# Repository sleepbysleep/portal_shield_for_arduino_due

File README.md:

# portal_shield_for_arduino_due
KiCad project - 2 x RS232 with RS485 option, 1 x relay, and 1 x opto-coupler

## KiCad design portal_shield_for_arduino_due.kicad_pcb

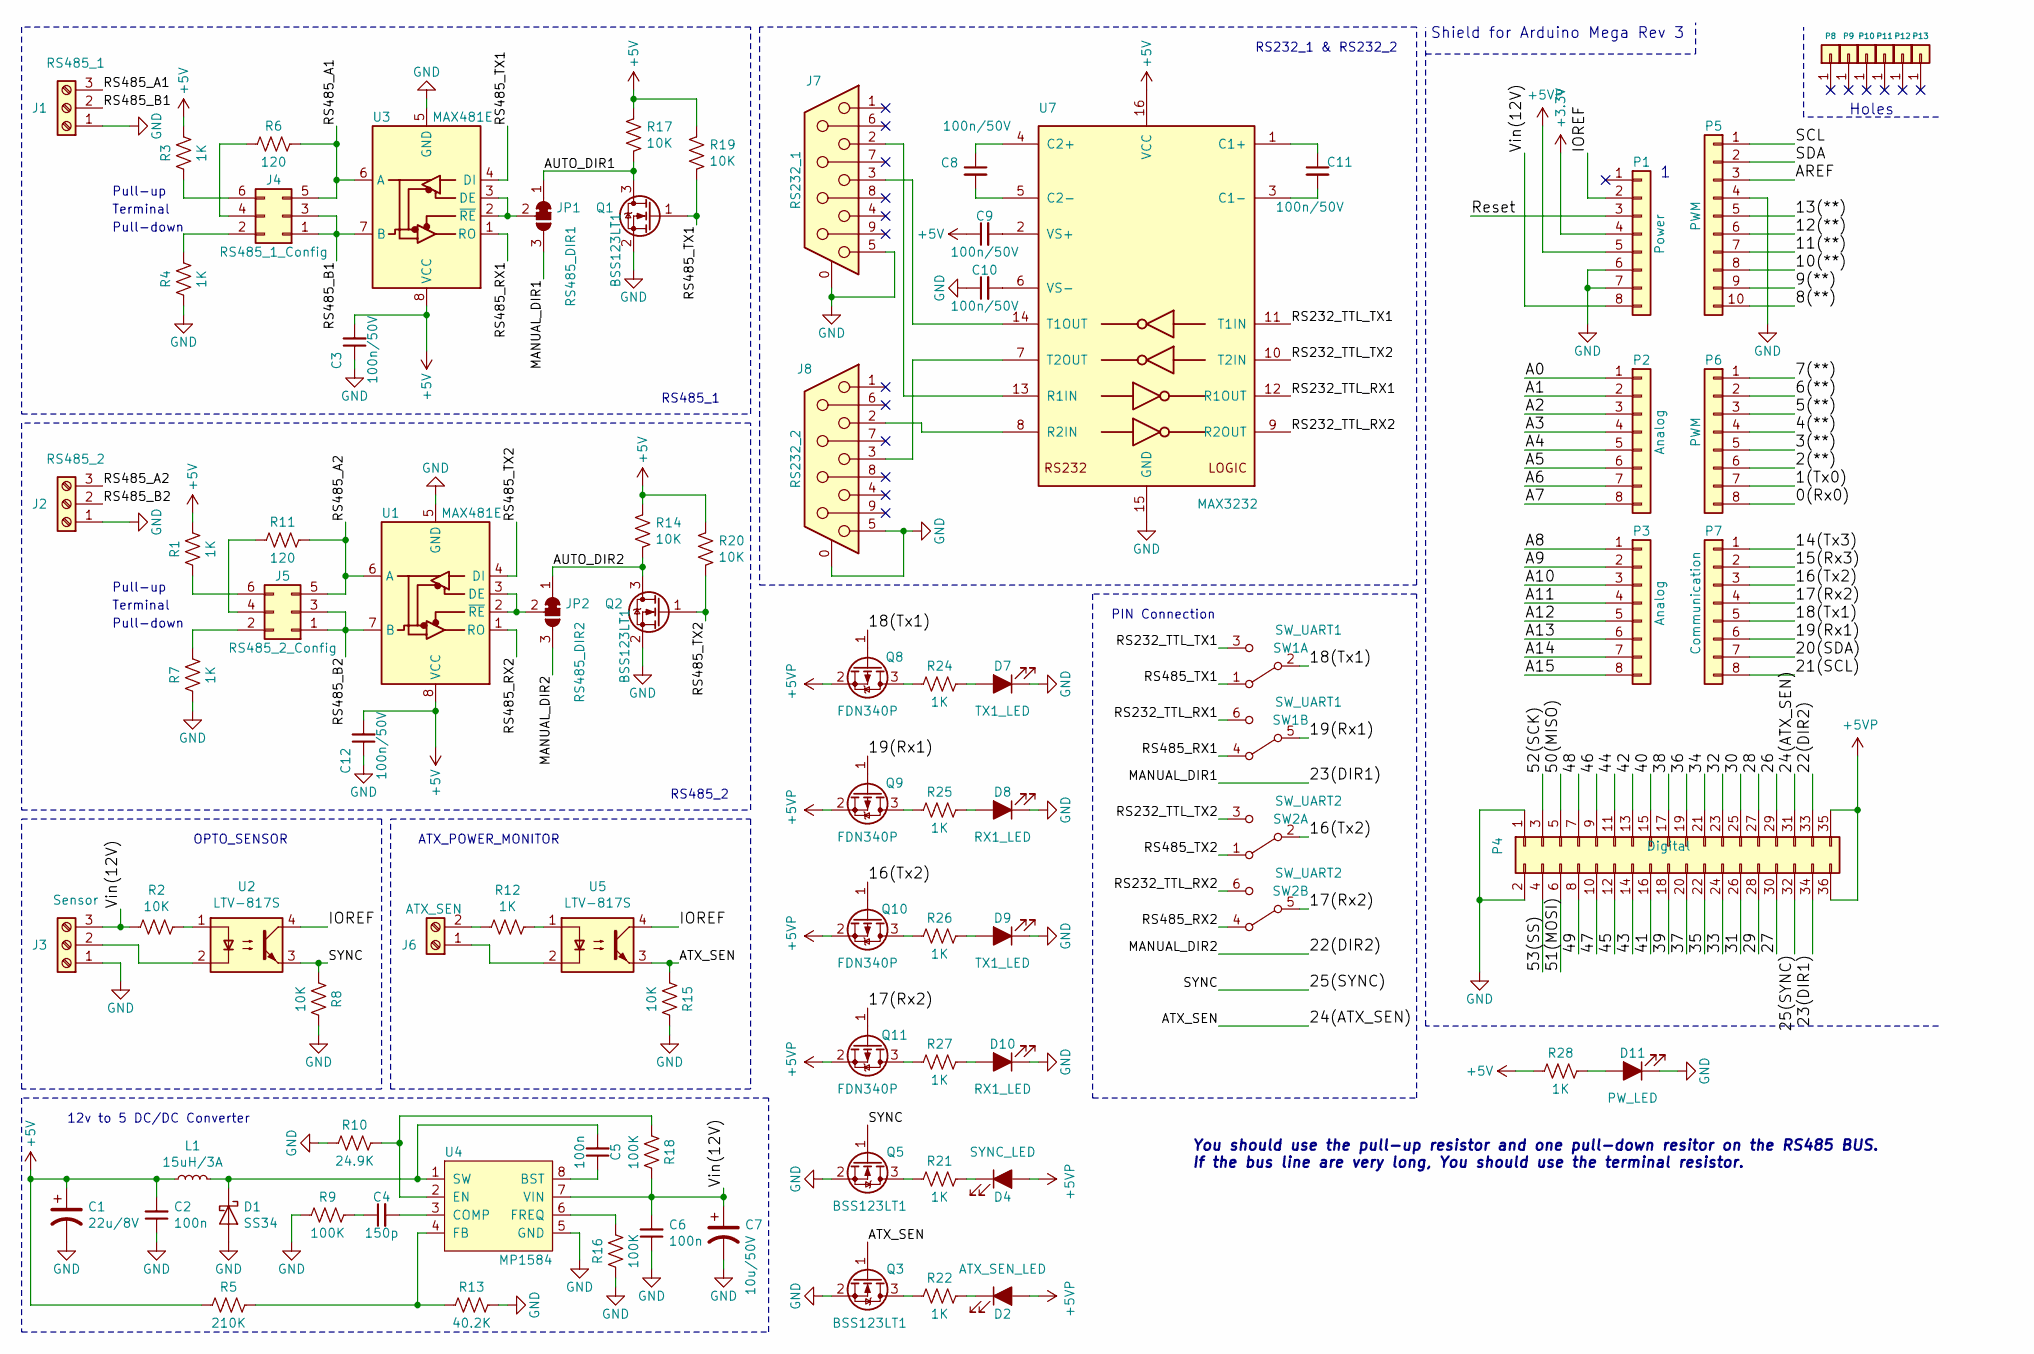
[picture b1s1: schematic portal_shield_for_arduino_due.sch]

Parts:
C1: 22u/8V; C_1206_3216Metric
C2, C5, C6: 100n; C_0805_2012Metric
C3, C8, C9, C10, C11, C12: 100n/50V; C_0805_2012Metric
C4: 150p; C_0805_2012Metric
C7: 10u/50V; C_1206_3216Metric
D1: SS34; D_SOD-123F
D2: ATX_SEN_LED; LED_0805_2012Metric
D4: SYNC_LED; LED_0805_2012Metric
D7, D9: TX1_LED; LED_0805_2012Metric
D8, D10: RX1_LED; LED_0805_2012Metric
D11: PW_LED; LED_0805_2012Metric
J1: RS485_1; TerminalBlock_Phoenix_PTSA-1,5-3-3.5-Z_1x3_P3.5mm_Vertical
J2: RS485_2; TerminalBlock_Phoenix_PTSA-1,5-3-3.5-Z_1x3_P3.5mm_Vertical
J3: Sensor; TerminalBlock_Phoenix_PTSA-1,5-3-3.5-Z_1x3_P3.5mm_Vertical
J4: RS485_1_Config; PinHeader_2x03_P2.54mm_Vertical
J5: RS485_2_Config; PinHeader_2x03_P2.54mm_Vertical
J6: ATX_SEN; TerminalBlock_Phoenix_PTSA-1,5-2-3.5-Z_1x2_P3.5mm_Vertical
J7: RS232_1; DSUB-9_Female_Vertical_P2.77x2.84mm_MountingHoles
J8: RS232_2; DSUB-9_Female_Vertical_P2.77x2.84mm_MountingHoles
JP1: RS485_DIR1; SolderJumper-3_P1.3mm_Open_Pad1.0x1.5mm
JP2: RS485_DIR2; SolderJumper-3_P1.3mm_Open_Pad1.0x1.5mm
L1: 15uH/3A; L_Abracon_ASPI_0630LR
P1: Power; Socket_Strip_Arduino_1x08
P2, P3: Analog; Socket_Strip_Arduino_1x08
P4: Digital; Socket_Strip_Arduino_2x18
P5: PWM; Socket_Strip_Arduino_1x10
P6: PWM; Socket_Strip_Arduino_1x08
P7: Communication; Socket_Strip_Arduino_1x08
P8, P9, P10, P11, P12, P13: CONN_01X01; Arduino_1pin
Q1, Q2, Q3, Q5: BSS123LT1; SOT-23
Q8, Q9, Q10, Q11: FDN340P; SOT-23
R1, R3, R4, R7, R12, R21, R22, R24, R25, R26, R27, R28: 1K; R_0805_2012Metric
R2, R8, R14, R15, R17, R19, R20: 10K; R_0805_2012Metric
R5: 210K; R_0805_2012Metric
R6, R11: 120; R_0805_2012Metric
R9, R16, R18: 100K; R_0805_2012Metric
R10: 24.9K; R_0805_2012Metric
R13: 40.2K; R_0805_2012Metric
SW1: SW_UART1; SW_CK_AYZ020AGRLC_DPDT_Straight
SW2: SW_UART2; SW_CK_AYZ020AGRLC_DPDT_Straight
U1, U3: MAX481E; SOIC-8_3.9x4.9mm_P1.27mm
U2, U5: LTV-817S; SMDIP-4_W9.53mm
U4: MP1584; SOIC8E
U7: MAX3232; TSSOP-16_4.4x5mm_P0.65mm

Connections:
+3V3: P1.4
+5V: C1.1, C2.2, C3.2, C9.1, C12.2, L1.1, R1.1, R3.1, R5.2, R14.1, R17.1, R19.1, R20.1, R28.2, U1.8 (VCC), U3.8 (VCC), U7.16 (VCC)
+5VP: D2.2 (A), D4.2 (A), P1.5, P4.35, P4.36, Q8.2 (S), Q9.2 (S), Q10.2 (S), Q11.2 (S)
/0(Rx0): P6.8
/1(Tx0): P6.7
/2(**): P6.6
/3(**): P6.5
/4(**): P6.4
/5(**): P6.3
/6(**): P6.2
/7(**): P6.1
/8(**): P5.10
/9(**): P5.9
/10(**): P5.8
/11(**): P5.7
/12(**): P5.6
/13(**): P5.5
/14(Tx3): P7.1
/15(Rx3): P7.2
/16(Tx2): P7.3, Q10.1 (G), SW2.2 (B)
/17(Rx2): P7.4, Q11.1 (G), SW2.5 (B)
/18(Tx1): P7.5, Q8.1 (G), SW1.2 (B)
/19(Rx1): P7.6, Q9.1 (G), SW1.5 (B)
/20(SDA): P7.7
/21(SCL): P7.8
/22(DIR2): JP2.3 (B), P4.33
/23(DIR1): JP1.3 (B), P4.34
/24(ATX_SEN): P4.31, Q3.1 (G), R15.2, U5.3
/25(SYNC): P4.32, Q5.1 (G), R8.2, U2.3
/26: P4.29
/27: P4.30
/28: P4.27
/29: P4.28
/30: P4.25
/31: P4.26
/32: P4.23
/33: P4.24
/34: P4.21
/35: P4.22
/36: P4.19
/37: P4.20
/38: P4.17
/39: P4.18
/40: P4.15
/41: P4.16
/42: P4.13
/43: P4.14
/44: P4.11
/45: P4.12
/46: P4.9
/47: P4.10
/48: P4.7
/49: P4.8
/50(MISO): P4.5
/51(MOSI): P4.6
/52(SCK): P4.3
/53(SS): P4.4
/A0: P2.1
/A1: P2.2
/A2: P2.3
/A3: P2.4
/A4: P2.5
/A5: P2.6
/A6: P2.7
/A7: P2.8
/A8: P3.1
/A9: P3.2
/A10: P3.3
/A11: P3.4
/A12: P3.5
/A13: P3.6
/A14: P3.7
/A15: P3.8
/AREF: P5.3
/AUTO_DIR1: JP1.1 (A), Q1.3 (D), R17.2
/AUTO_DIR2: JP2.1 (A), Q2.3 (D), R14.2
/IOREF: P1.2, U2.4, U5.4
/RS232_TTL_RX1: SW1.6 (C), U7.12 (R1OUT)
/RS232_TTL_RX2: SW2.6 (C), U7.9 (R2OUT)
/RS232_TTL_TX1: SW1.3 (C), U7.11 (T1IN)
/RS232_TTL_TX2: SW2.3 (C), U7.10 (T2IN)
/RS485_A1: J1.3, J4.5, R6.1, U3.6 (A)
/RS485_A2: J2.3, J5.5, R11.1, U1.6 (A)
/RS485_B1: J1.2, J4.1, J4.3, U3.7 (B)
/RS485_B2: J2.2, J5.1, J5.3, U1.7 (B)
/RS485_RX1: SW1.4 (A), U3.1 (RO)
/RS485_RX2: SW2.4 (A), U1.1 (RO)
/RS485_TX1: Q1.1 (G), R19.2, SW1.1 (A), U3.4 (DI)
/RS485_TX2: Q2.1 (G), R20.2, SW2.1 (A), U1.4 (DI)
/Reset: P1.3
/SCL: P5.1
/SDA: P5.2
/Vin(12V): C6.2, C7.1, J3.3, P1.8, R2.2, R18.2, U4.7 (VIN)
GND: C1.2, C2.1, C3.1, C6.1, C7.2, C10.1, C12.1, D1.2 (A), D7.1 (K), D8.1 (K), D9.1 (K), D10.1 (K), D11.1 (K), J1.1, J2.1, J3.1, J7.0 (PAD), J7.5, J8.0 (PAD), J8.5, P1.6, P1.7, P4.1, P4.2, P5.4, Q1.2 (S), Q2.2 (S), Q3.2 (S), Q5.2 (S), R4.2, R7.2, R8.1, R9.2, R10.2, R13.1, R15.1, R16.2, U1.5 (GND), U3.5 (GND), U4.5 (GND), U7.15 (GND)
unnamed: C4.1, R9.1
unnamed: C4.2, U4.3 (COMP)
unnamed: C5.1, U4.8 (BST)
unnamed: C5.2, D1.1 (K), L1.2, U4.1 (SW)
unnamed: C8.1, U7.4 (C2+)
unnamed: C8.2, U7.5 (C2-)
unnamed: C9.2, U7.2 (VS+)
unnamed: C10.2, U7.6 (VS-)
unnamed: C11.1, U7.1 (C1+)
unnamed: C11.2, U7.3 (C1-)
unnamed: D2.1 (K), R22.1
unnamed: D4.1 (K), R21.1
unnamed: D7.2 (A), R24.1
unnamed: D8.2 (A), R25.1
unnamed: D9.2 (A), R26.1
unnamed: D10.2 (A), R27.1
unnamed: D11.2 (A), R28.1
unnamed: J3.2, U2.2
unnamed: J4.2, R4.1
unnamed: J4.4, R6.2
unnamed: J4.6, R3.2
unnamed: J5.2, R7.1
unnamed: J5.4, R11.2
unnamed: J5.6, R1.2
unnamed: J6.1, U5.2
unnamed: J6.2, R12.2
unnamed: J7.2, U7.13 (R1IN)
unnamed: J7.3, U7.14 (T1OUT)
unnamed: J8.2, U7.8 (R2IN)
unnamed: J8.3, U7.7 (T2OUT)
unnamed: JP1.2 (C), U3.2 (~RE), U3.3 (DE)
unnamed: JP2.2 (C), U1.2 (~RE), U1.3 (DE)
unnamed: Q3.3 (D), R22.2
unnamed: Q5.3 (D), R21.2
unnamed: Q8.3 (D), R24.2
unnamed: Q9.3 (D), R25.2
unnamed: Q10.3 (D), R26.2
unnamed: Q11.3 (D), R27.2
unnamed: R2.1, U2.1
unnamed: R10.1, R18.1, U4.2 (EN)
unnamed: R12.1, U5.1
unnamed: R5.1, R13.2, U4.4 (FB)
unnamed: R16.1, U4.6 (FREQ)

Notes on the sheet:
Shield for Arduino Mega Rev 3
Holes
RS232_1 & RS232_2
RS485_1
OPTO_SENSOR
PIN Connection
You should use the pull-up resistor and one pull-down resitor on the RS485 BUS. If the bus line are very long, You should use the terminal resistor.
Pull-up
Terminal
Pull-down
12v to 5 DC/DC Converter
RS485_2
ATX_POWER_MONITOR

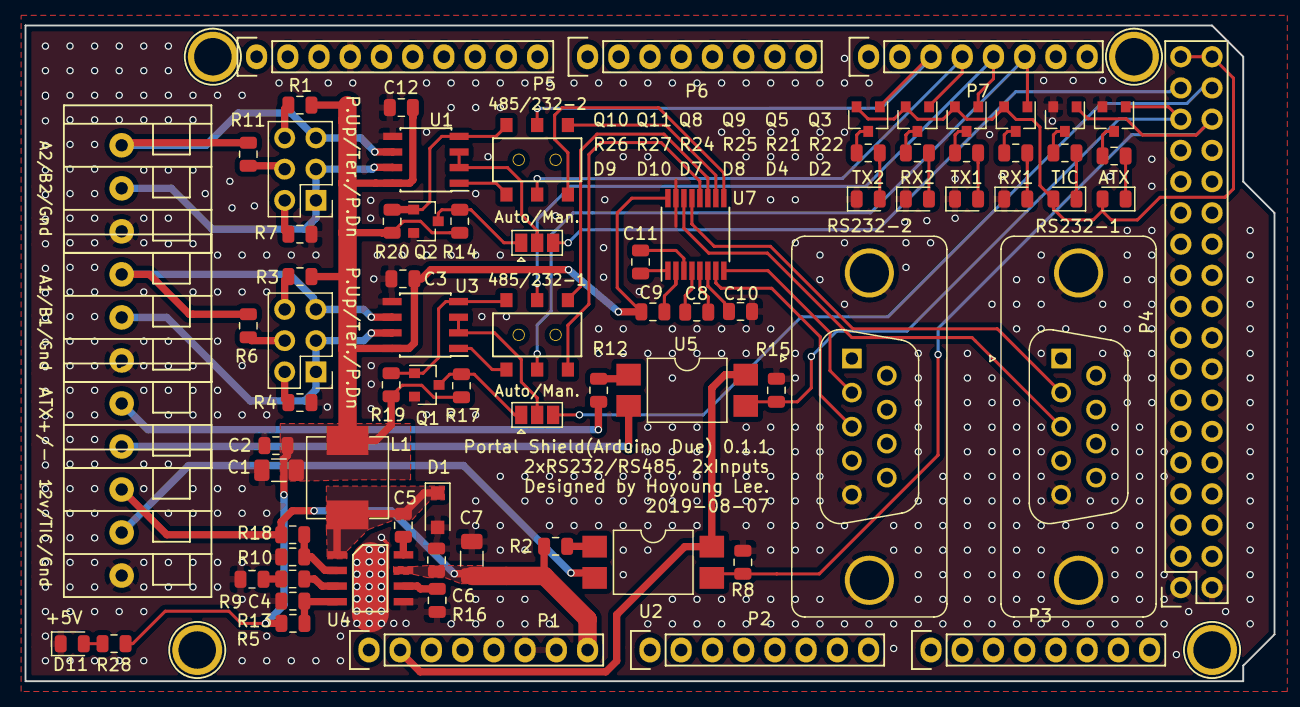
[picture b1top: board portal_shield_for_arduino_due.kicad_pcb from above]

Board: 2 copper layers, 101.6 x 53.3 mm, 85 parts (0 on the bottom side), 70 nets.

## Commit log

2019-05-29 Modify: RS485_2 is removed, and two Mosfet power switchs are added.
2019-05-29 Modified: visual enhancement is added
2019-05-31 The option of switching/powering in Cam and Illumination are added
2019-06-09 Down-sizing with 2xrs232/rs485, and 2xinputs, and renamed into portal_shield_for_arduino_due
2019-08-13 modified to expand the interval between DSUB9s, and add labels of terminals
